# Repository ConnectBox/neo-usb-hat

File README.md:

This branch is Depricated

Please use branch https://github.com/ConnectBox/Circuit-Design/tree/Version5.0

# neo-usb-hat
This repo contains the schematic and KiCAD design files for the NEO-USB-HAT.  This is a daugherboard to add an extra USB port and power input to a NanoPi NEO.

##Version 0 Design
This version contains the KiCAD design for the NEO-USB-HAT that includes: 1 additional USB Type A port that is wired to the NEO's expansion pins, and a microUSB power input that runs through a voltage regulator that also powers the NEO through the expansion GPIO pins.

####Version 1: Schematic

[Schematic Link](https://github.com/ConnectBox/neo-usb-hat/blob/master/Revision0/NEO_USB_HAT_14.06.2017.pdf  "Schematic")

####Version 1: PCB Design

####Finished Product:

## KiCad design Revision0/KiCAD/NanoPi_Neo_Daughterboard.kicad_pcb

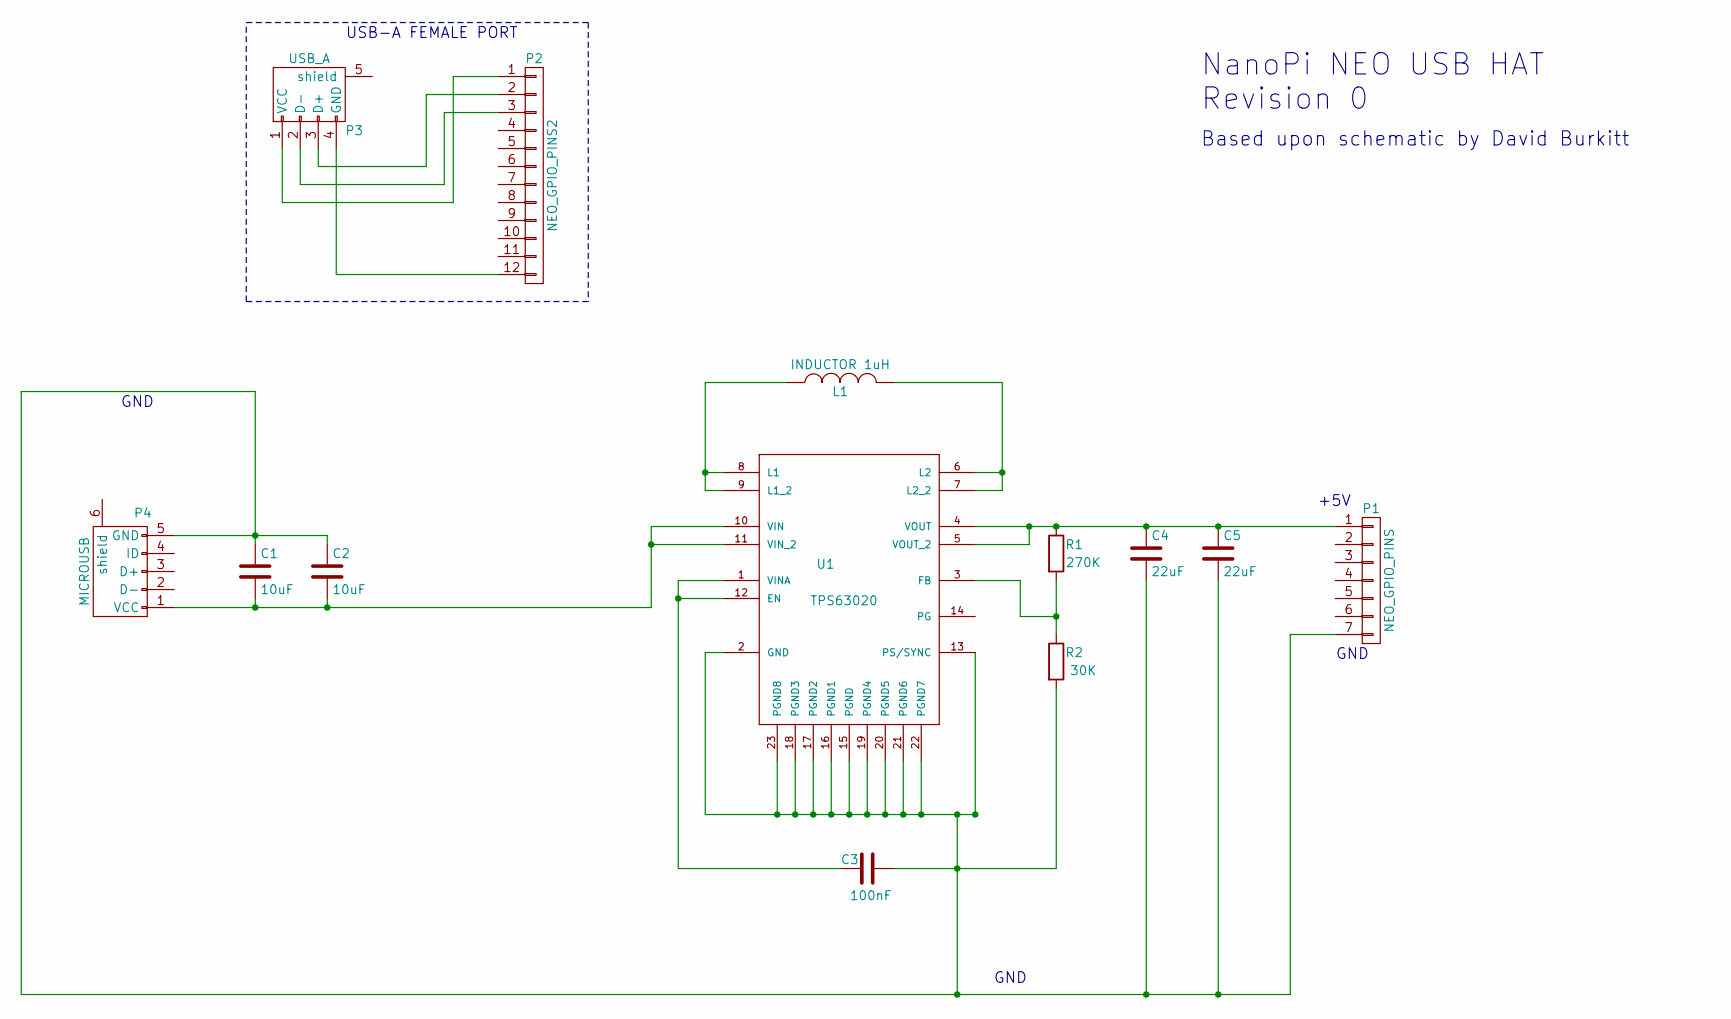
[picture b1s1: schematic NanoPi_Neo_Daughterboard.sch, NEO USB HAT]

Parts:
C1, C2: 10uF; c_0805
C3: 100nF; c_0805
C4, C5: 22uF; c_0805
L1: INDUCTOR 1uH; BOURNS-SDR0403
P1: NEO_GPIO_PINS; pin_strip_7
P2: NEO_GPIO_PINS2; pin_strip_12
P3: USB_A
P4: MICROUSB; USB_Micro-B
R1: 270K; r_0805
R2: 30K; r_0805
U1: TPS63020; QFN14-3X4MM

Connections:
unnamed: C1.1, C2.1, C3.1, C4.2, C5.2, P1.7, P4.5 (GND), R2.2, U1.2 (GND), U1.13 (PS/SYNC), U1.15 (PGND), U1.16 (PGND1), U1.17 (PGND2), U1.18 (PGND3), U1.19 (PGND4), U1.20 (PGND5), U1.21 (PGND6), U1.22 (PGND7), U1.23 (PGND8)
unnamed: C1.2, C2.2, P4.1 (VCC), U1.10 (VIN), U1.11 (VIN_2)
unnamed: C3.2, U1.1 (VINA), U1.12 (EN)
unnamed: C4.1, C5.1, P1.1, R1.1, U1.4 (VOUT), U1.5 (VOUT_2)
unnamed 4: L1.1, U1.8 (L1), U1.9 (L1_2); also elsewhere on the board
unnamed 5: L1.2, U1.6 (L2), U1.7 (L2_2); also elsewhere on the board
unnamed: P2.1, P3.1 (VCC)
unnamed: P2.2, P3.3 (D+)
unnamed: P2.3, P3.2 (D-)
unnamed: P2.12, P3.4 (GND)
unnamed: R1.2, R2.1, U1.3 (FB)

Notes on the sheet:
USB-A FEMALE PORT
GND
+5V
GND
Based upon schematic by David Burkitt
NanoPi NEO USB HAT Revision 0

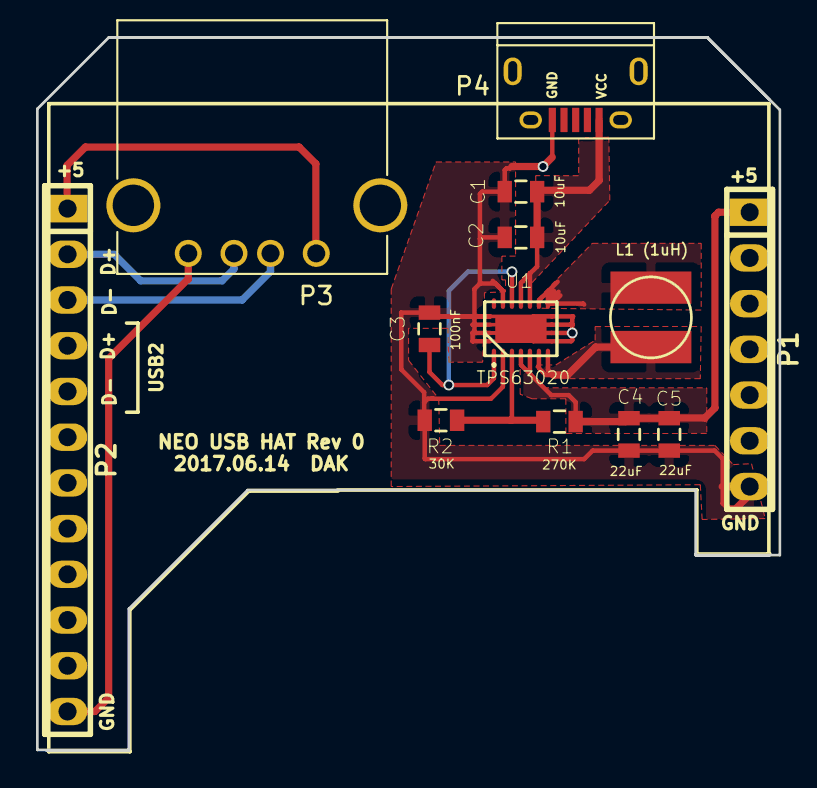
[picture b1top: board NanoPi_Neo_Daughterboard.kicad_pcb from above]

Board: 2 copper layers, 41.2 x 39.6 mm, 13 parts (0 on the bottom side), 11 nets.

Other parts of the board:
L1 (1uH): INDUCTOR 1uH; BOURNS-SDR0403

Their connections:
unnamed 4: L1 (1uH).1; also elsewhere on the board
unnamed 5: L1 (1uH).2; also elsewhere on the board

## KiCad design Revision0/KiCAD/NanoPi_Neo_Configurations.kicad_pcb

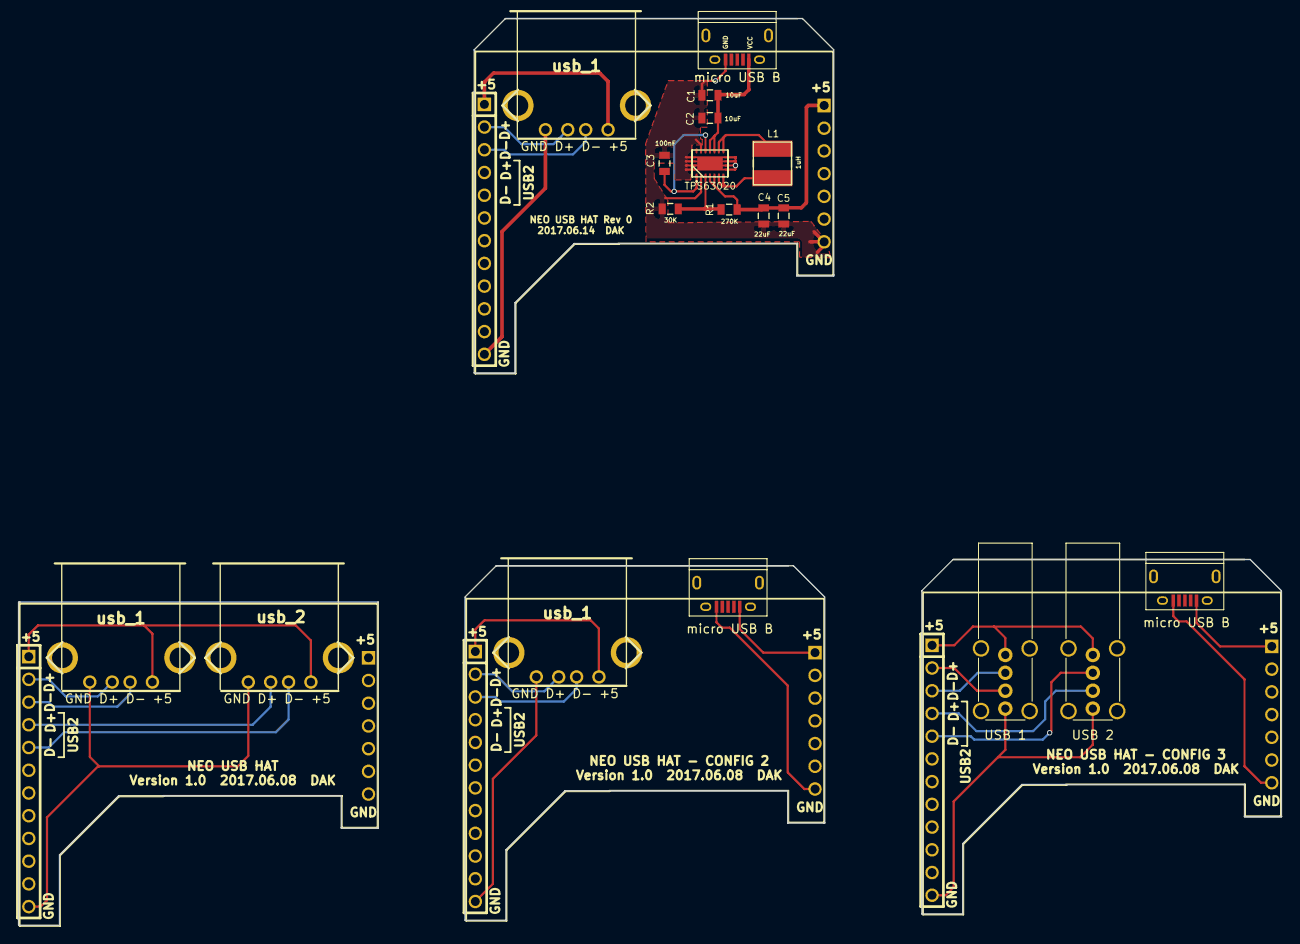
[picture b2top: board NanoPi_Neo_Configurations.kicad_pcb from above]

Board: 2 copper layers, 141.2 x 101.4 mm, 18 parts (0 on the bottom side), 7 nets.

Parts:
C1, C2: 10uF; 0805
C3: 100nF; 0805
C4, C5: 22uF; 0805
L1: 1uH; SDR0403
R1: 270K; 0805
R2: 30K; 0805
TPS63020: QFN14-3X4MM
USB 1, USB 2: USB_A_Vertical
micro USB B: USB_Micro-B
micro USB B#2, micro USB B#3: USB_Micro-B
usb_1, usb_1#2, usb_1#3, usb_2: conn_usb_A

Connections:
FB: R1.1, R2.1, TPS63020.3
GND: C1.2, C2.2, C3.2, C4.2, C5.2, R2.2, TPS63020.2, TPS63020.13, TPS63020.15, TPS63020.16, TPS63020.17, TPS63020.18, TPS63020.19, TPS63020.20, TPS63020.21, TPS63020.22, TPS63020.23
unnamed: C3.1, TPS63020.1, TPS63020.12
unnamed: L1.1, TPS63020.8, TPS63020.9
unnamed: L1.2, TPS63020.6, TPS63020.7
VIN: C1.1, C2.1, TPS63020.10, TPS63020.11
VOUT: C4.1, C5.1, R1.2, TPS63020.4, TPS63020.5

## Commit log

2017-07-21 updated links
2017-07-21 fixed links
2018-06-11 Added in the 2018Q2 Production
    Schematics and KiCAD design files
2019-08-02 Deprecated branch
